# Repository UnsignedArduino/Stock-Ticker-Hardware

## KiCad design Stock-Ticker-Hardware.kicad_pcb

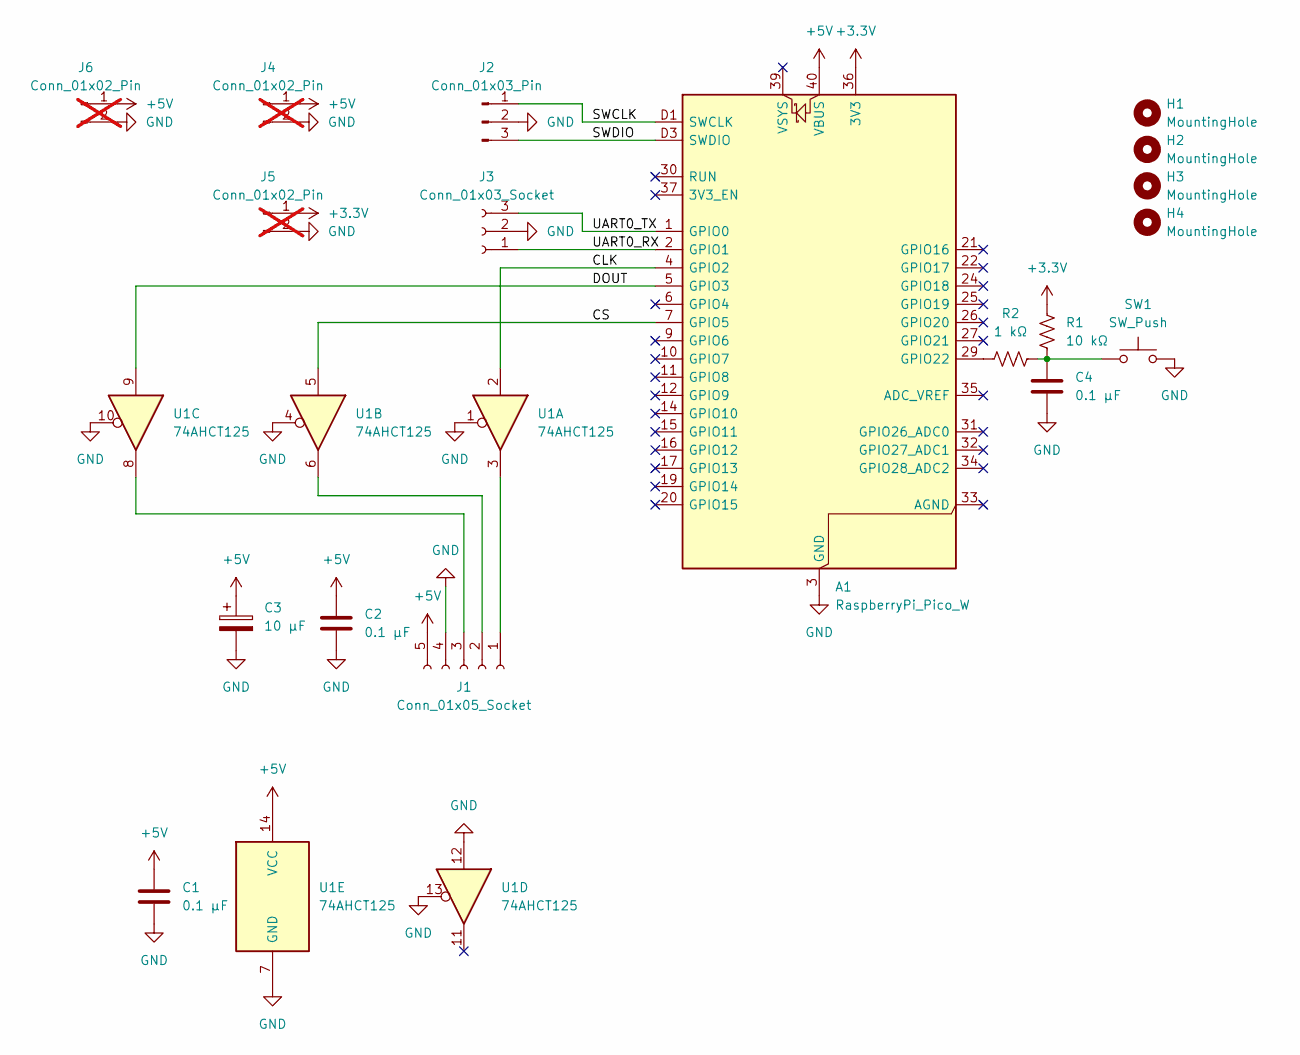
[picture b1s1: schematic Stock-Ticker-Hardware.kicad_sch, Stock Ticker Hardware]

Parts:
A1: RaspberryPi_Pico_W; RaspberryPi_Pico_W_SMD_HandSolder
C1, C2, C4: 0.1 μF; C_Disc_D5.0mm_W2.5mm_P2.50mm
C3: 10 μF; CP_Radial_D4.0mm_P2.00mm
H1, H2, H3, H4: MountingHole; MountingHole_2.7mm_M2.5
J1: Conn_01x05_Socket; JST_XH_B5B-XH-A_1x05_P2.50mm_Vertical
J2: Conn_01x03_Pin; PinHeader_1x03_P2.54mm_Vertical
J3: Conn_01x03_Socket; PinSocket_1x03_P2.54mm_Vertical
J4, J5, J6: Conn_01x02_Pin; PinHeader_1x02_P2.54mm_Vertical; not fitted
R1: 10 kΩ; R_Axial_DIN0207_L6.3mm_D2.5mm_P10.16mm_Horizontal
R2: 1 kΩ; R_Axial_DIN0207_L6.3mm_D2.5mm_P10.16mm_Horizontal
SW1: SW_Push; SW_PUSH-12mm
U1: 74AHCT125; DIP-14_W7.62mm

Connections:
+3.3V: A1.36 (3V3), J5.1, R1.1
+5V: A1.40 (VBUS), C1.1, C2.1, C3.1, J1.5, J4.1, J6.1, U1.14 (VCC)
/CLK: A1.4 (GPIO2), U1.2
/CS: A1.7 (GPIO5), U1.5
/DOUT: A1.5 (GPIO3), U1.9
/SWCLK: A1.D1 (SWCLK), J2.1
/SWDIO: A1.D3 (SWDIO), J2.3
/UART0_RX: A1.2 (GPIO1), J3.1
/UART0_TX: A1.1 (GPIO0), J3.3
GND: A1.3 (GND), A1.8 (GND), A1.13 (GND), A1.18 (GND), A1.23 (GND), A1.28 (GND), A1.38 (GND), A1.D2 (GND), C1.2, C2.2, C3.2, C4.2, J1.4, J2.2, J3.2, J4.2, J5.2, J6.2, SW1.2, U1.1, U1.4, U1.7 (GND), U1.10, U1.12, U1.13
unnamed: A1.29 (GPIO22), R2.1
unnamed: C4.1, R1.2, R2.2, SW1.1
unnamed: J1.1, U1.3
unnamed: J1.2, U1.6
unnamed: J1.3, U1.8

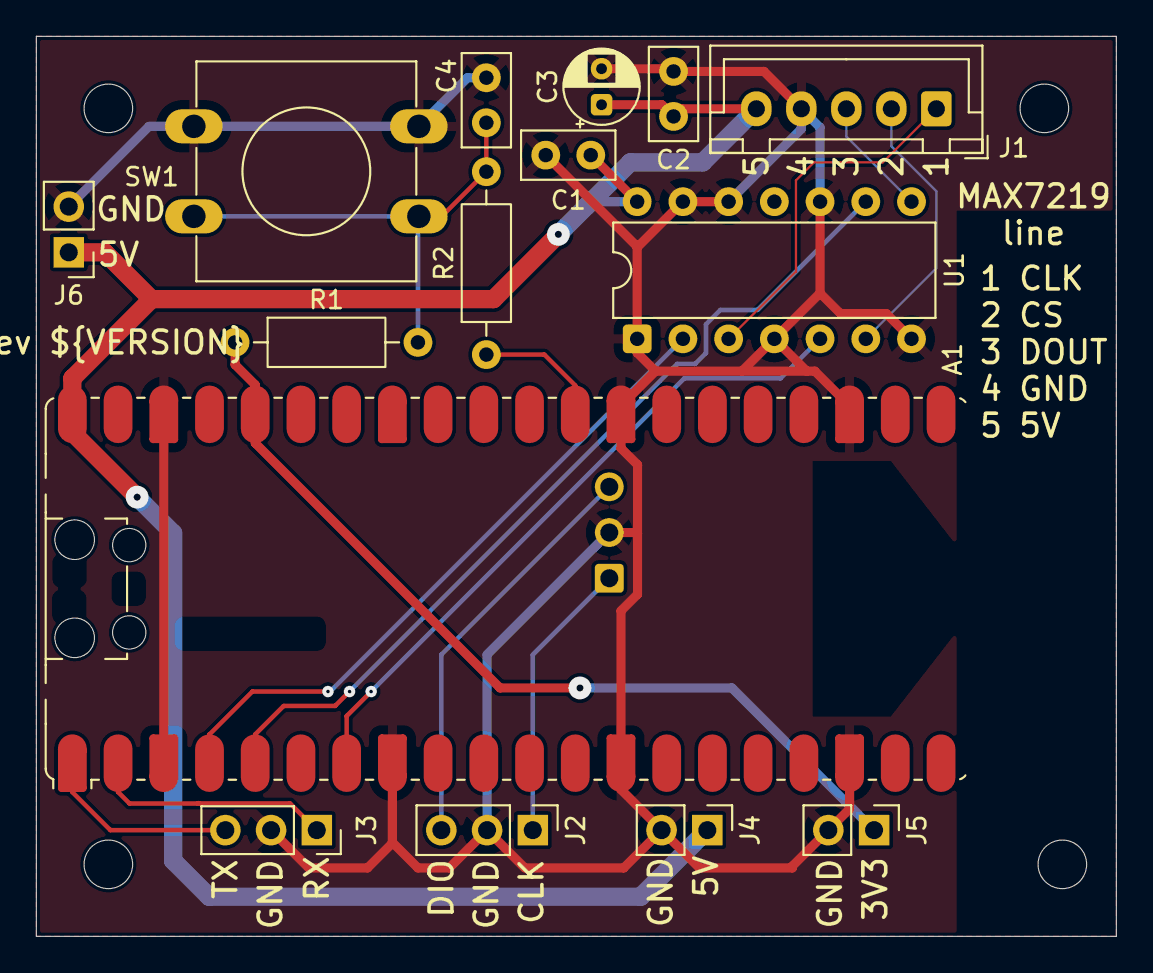
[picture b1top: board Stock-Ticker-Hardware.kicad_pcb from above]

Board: 2 copper layers, 60.0 x 50.0 mm, 19 parts (0 on the bottom side), 15 nets.

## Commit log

2025-07-19 Init and modify from template
2025-07-19 Start schematic
2025-07-19 Finish basic schematic
2025-12-22 Correct wiring from Pico to JST XH
2025-12-22 Place on PCB
2025-12-23 Add connectors for SWD and UART for easy debugging
2025-12-23 Finish simple PCB
2025-12-24 Better schematic with level shifter, decoup caps, delete PCB
2025-12-24 Component layout once again
2025-12-24 Finish routing
2025-12-24 Finish actual routing this time
2025-12-24 Increase 5v trace width
2025-12-24 Add silk text pin labels
2025-12-25 Points for power rails and ground
2025-12-25 Shift pin headers up for silk text space
2025-12-25 Move info silk around
2025-12-25 Cleanup tracks
2026-01-09 Add DNP on some headers
